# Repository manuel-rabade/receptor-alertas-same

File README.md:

# Receptor alertas SAME

Este deposito contiene el diseño de hardware y código fuente de mi trabajo de tesis, titulado [Sistema embebido para recibir alertas de riesgo codificadas con el protocolo SAME](http://www.ptolomeo.unam.mx:8080/xmlui/handle/RepoFi/18971), el cual realice para obtener el título de Ingeniero en Computación en la Facultad de Ingeniería de la Universidad Nacional Autónoma de México.

Como resultado de mi proyecto de titulación, se desarrolló un sistema embebido capaz de recibir alertas de riesgo transmitidas mediante el protocolo SAME y difundirlas a través de medios visuales, auditivos o electrónicos. Además, se documentan las bases técnicas para el desarrollo de productos o servicios que amplíen el aprovechamiento y la cobertura de los sistemas de alerta de riesgos.

## Organización

- [hardware](hardware): Diagrama esquemático, diseño de la placa electrónica y lista de componentes electrónicos del receptor.
- [software](software): Implementación del software del receptor. Código fuente de las pruebas unitarias y de integración.
- [logger](logger): Scripts y configuración para recolectar registros de operación.
- [prototipo](prototipo): Diagrama esquemático y software del prototipo del receptor.

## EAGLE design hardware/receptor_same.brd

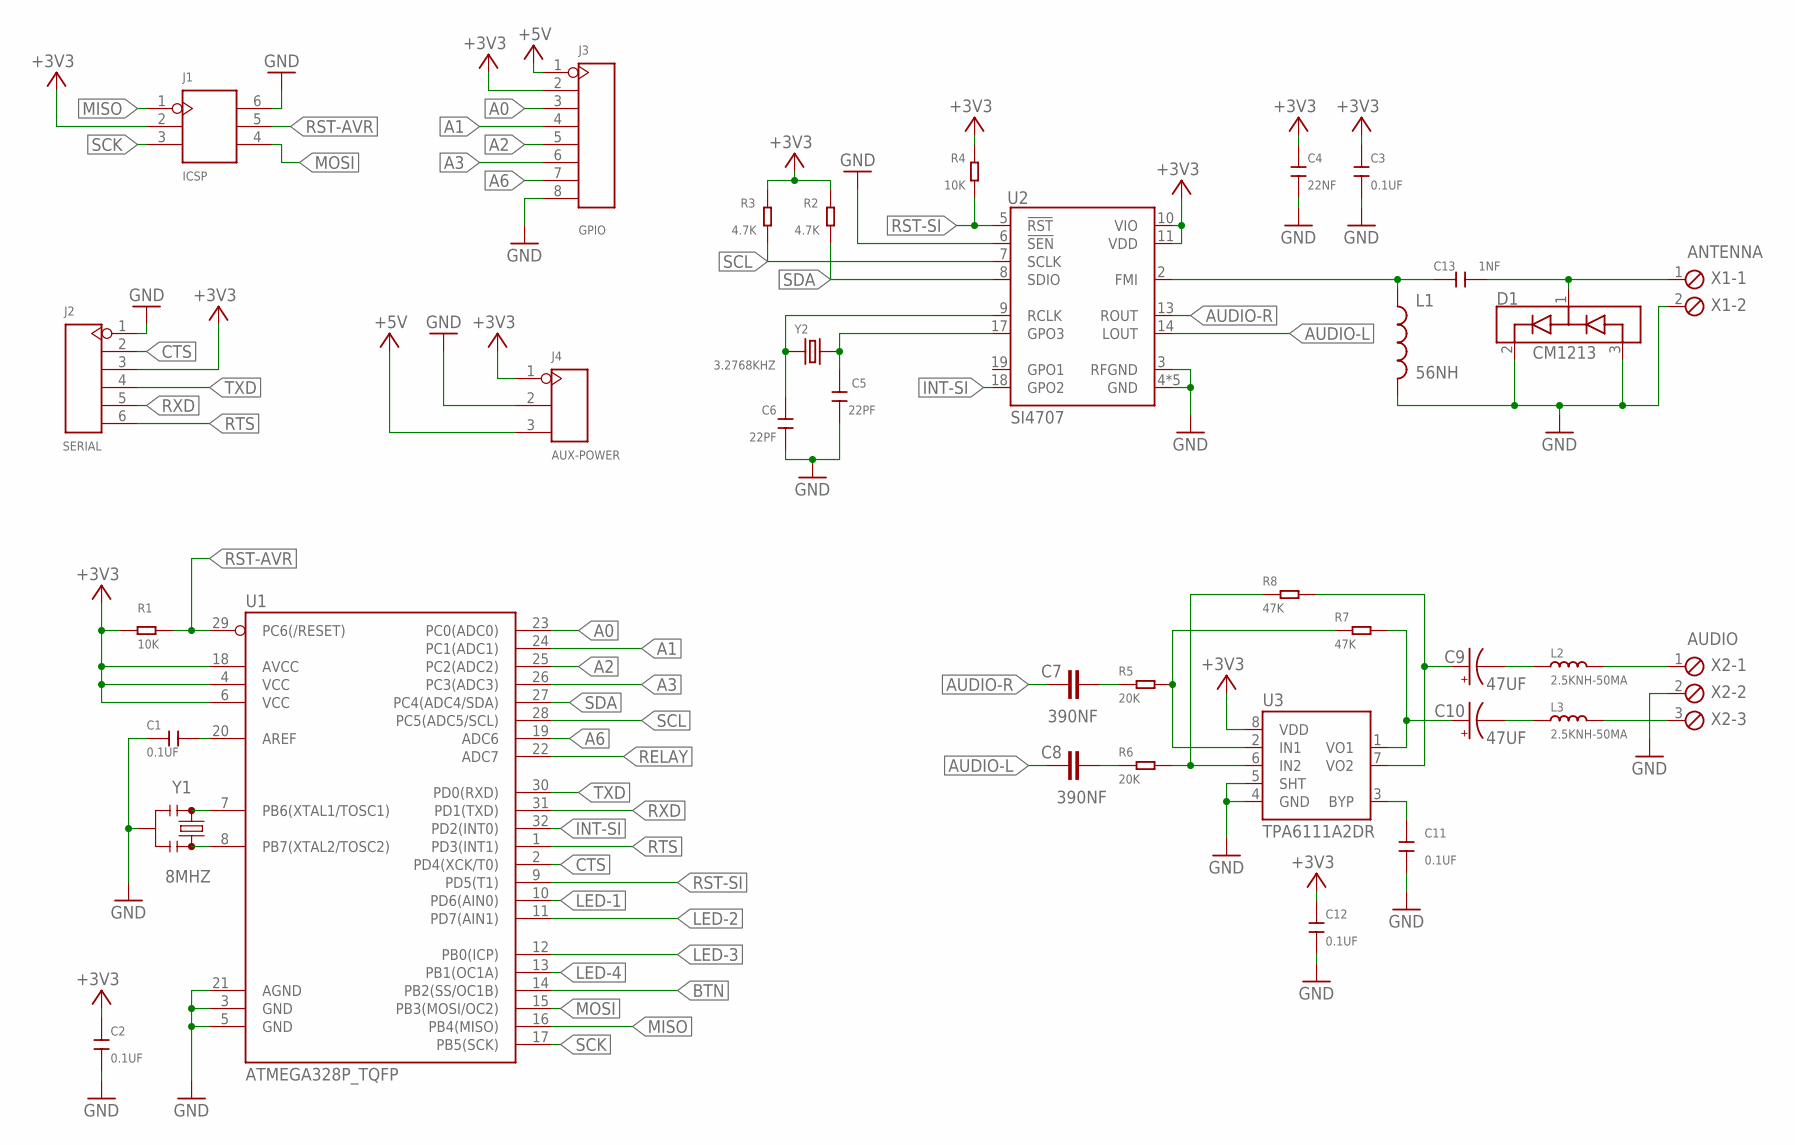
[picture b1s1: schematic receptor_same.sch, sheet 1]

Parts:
C1, C2, C3, C11, C12: 0.1UF; C0603
C4: 22NF; C0603
C5, C6: 22PF; C0603
C7, C8: 390NF; 0603; MPN CC0603KRX7R6BB394
C9, C10: 47UF; EIA3528; MPN TAJB476K010RNJ
C13: 1NF; C0603
D1: CM1213; SPARKFUN-DISCRETESEMI_SOT23-3; MPN CM1213A-01SO
J1: ICSP; H2X3-2.54
J2: SERIAL; H6-2.54
J3: GPIO; H8-2.54
J4: AUX-POWER; H3-2.54; MPN P125-1103A1BS116A1
L1: 56NH; SPARKFUN-PASSIVES_0603; MPN SDCL1608C56NJTDF
L2, L3: 2.5KNH-50MA; L0402; MPN BLM18BD252SN1D
R1, R4: 10K; R0603
R2, R3: 4.7K; R0603
R5, R6: 20K; R0603
R7, R8: 47K; R0603
U1: ATMEGA328P_TQFP; TQFP32-08; MPN ATMEGA328P-AU
U2: SI4707; SPARKFUN-RF_SI470X; MPN SI4707-B20-GM
U3: TPA6111A2DR; SO08; MPN TPA6111A2DR
X1: ANTENNA; 2POL254; MPN 1725656
X2: AUDIO; 3POL254; MPN 1725669
Y1: 8MHZ; RESONATOR-SMD-3.2X1.3; MPN CSTCE8M00G55-R0
Y2: 3.2768KHZ; X2-SMD-L2.0X1.2X0.55MM

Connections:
+3V3: C2.1, C3.1, C4.1, C12.1, J1.2, J2.3, J3.2, J4.1, R1.2, R2.1, R3.1, R4.1, U1.4 (VCC), U1.6 (VCC), U1.18 (AVCC), U2.10 (VIO), U2.11 (VDD), U3.8 (VDD); also elsewhere on the board
+5V: J3.1, J4.3; also elsewhere on the board
A0: J3.3, U1.23 (PC0(ADC0))
A1: J3.4, U1.24 (PC1(ADC1))
A2: J3.5, U1.25 (PC2(ADC2))
A3: J3.6, U1.26 (PC3(ADC3))
A6: J3.7, U1.19 (ADC6)
AUDIO-L: C8.1, U2.14 (LOUT)
AUDIO-R: C7.1, U2.13 (ROUT)
BTN: U1.14 (PB2(SS/OC1B)); also elsewhere on the board
CTS: J2.2, U1.2 (PD4(XCK/T0))
GND: C1.1, C2.2, C3.2, C4.2, C5.1, C6.1, C11.2, C12.2, D1.2 (VP), D1.3 (VN), J1.6, J2.1, J3.8, J4.2, L1.2, U1.3 (GND), U1.5 (GND), U1.21 (AGND), U2.3 (RFGND), U2.4 (GND), U2.6 (!SEN), U2.12 (GND), U2.15 (GND), U2.16 (GND), U2.21 (GND), U3.4 (GND), U3.5 (SHT), X1.2, X2.2, Y1.2; also elsewhere on the board
INT-SI: U1.32 (PD2(INT0)), U2.18 (GPO2)
L: L2.2, X2.1
LED-1: U1.10 (PD6(AIN0)); also elsewhere on the board
LED-2: U1.11 (PD7(AIN1)); also elsewhere on the board
LED-3: U1.12 (PB0(ICP)); also elsewhere on the board
LED-4: U1.13 (PB1(OC1A)); also elsewhere on the board
MISO: J1.1, U1.16 (PB4(MISO))
MOSI: J1.4, U1.15 (PB3(MOSI/OC2))
unnamed: U1.7 (PB6(XTAL1/TOSC1)), Y1.1
unnamed: U1.8 (PB7(XTAL2/TOSC2)), Y1.3
unnamed: C1.2, U1.20 (AREF)
unnamed: C5.2, U2.17 (GPO3), Y2.2
unnamed: C6.2, U2.9 (RCLK), Y2.1
unnamed: C13.1, L1.1, U2.2 (FMI)
unnamed: C7.2, R5.1
unnamed: C8.2, R6.1
unnamed: C11.1, U3.3 (BYP)
unnamed: R5.2, R7.1, U3.2 (IN1)
unnamed: C10.A (+), R7.2, U3.1 (VO1)
unnamed: R6.2, R8.1, U3.6 (IN2)
unnamed: C9.A (+), R8.2, U3.7 (VO2)
unnamed: C9.C (-), L2.1
unnamed: C10.C (-), L3.1
unnamed: C13.2, D1.1 (CH1), X1.1
R: L3.2, X2.3
RELAY: U1.22 (ADC7); also elsewhere on the board
RST-AVR: J1.5, R1.1, U1.29 (PC6(/RESET))
RST-SI: R4.2, U1.9 (PD5(T1)), U2.5 (!RST)
RTS: J2.6, U1.1 (PD3(INT1))
RXD: J2.5, U1.31 (PD1(TXD))
SCK: J1.3, U1.17 (PB5(SCK))
SCL: R3.2, U1.28 (PC5(ADC5/SCL)), U2.7 (SCLK)
SDA: R2.2, U1.27 (PC4(ADC4/SDA)), U2.8 (SDIO)
TXD: J2.4, U1.30 (PD0(RXD))

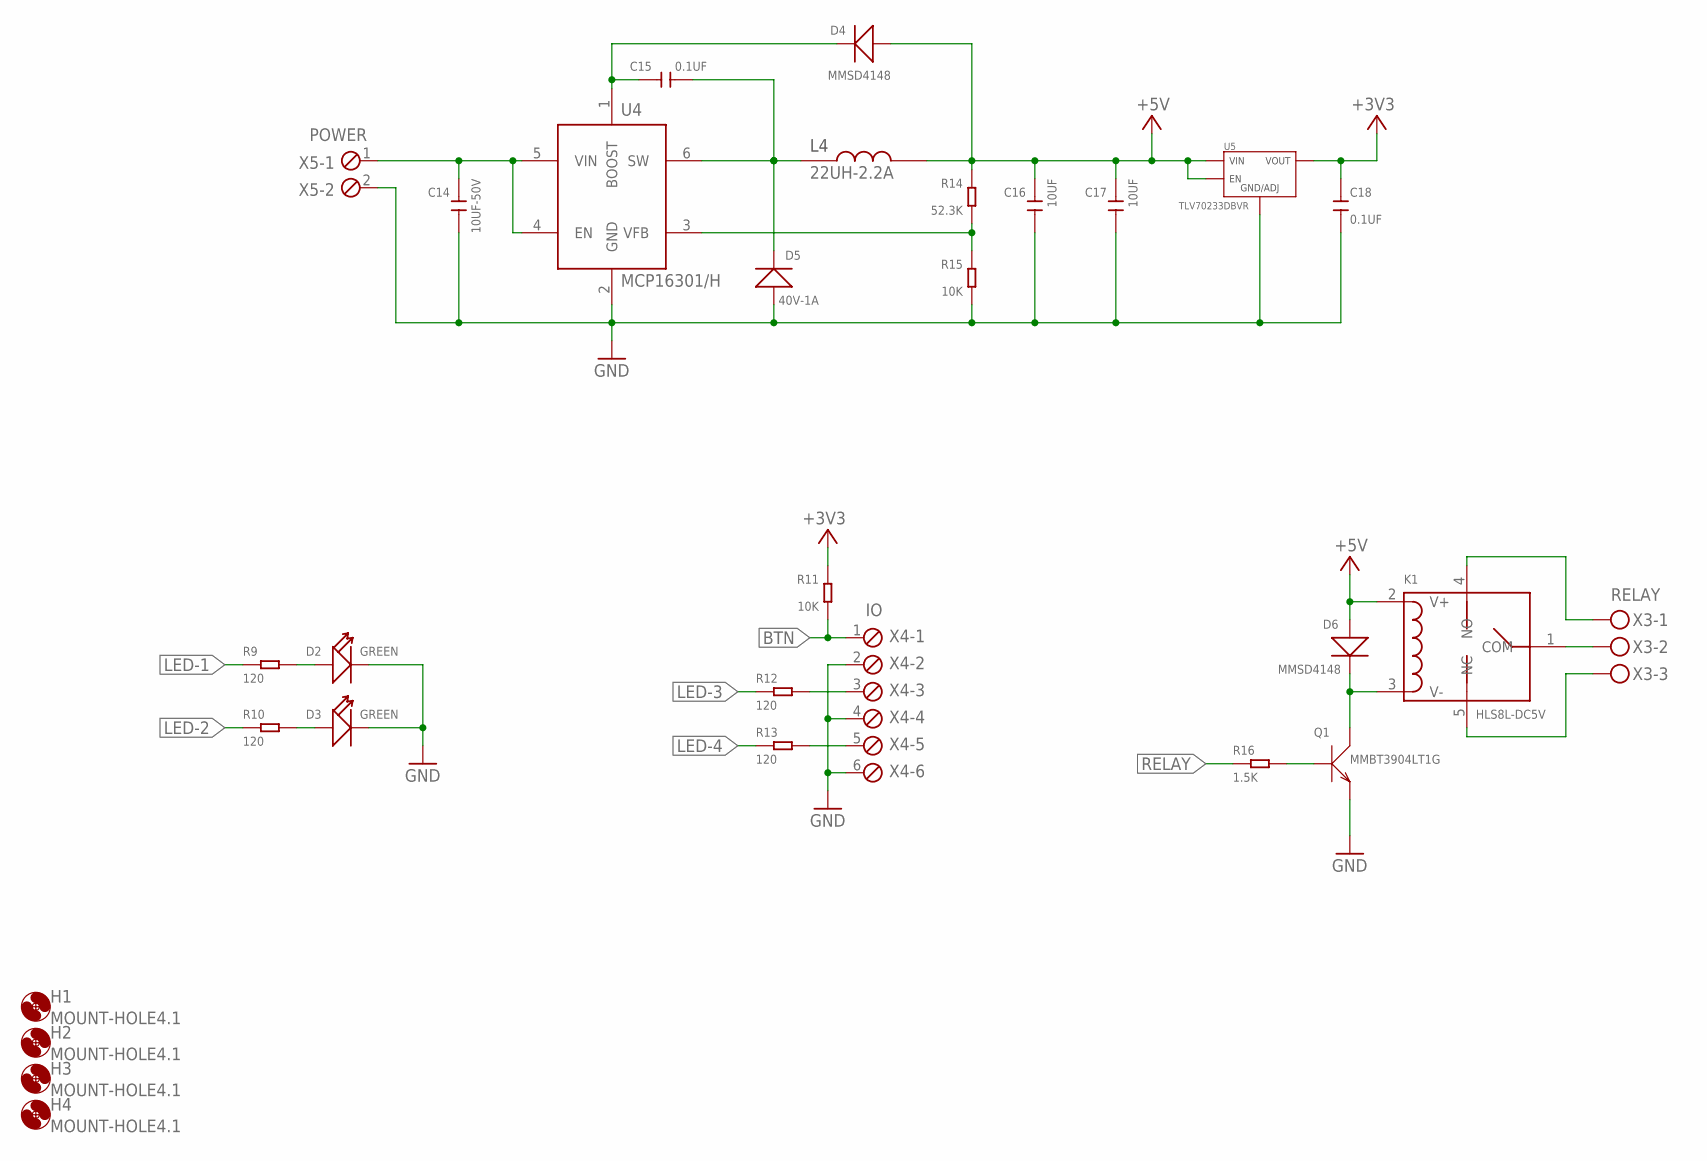
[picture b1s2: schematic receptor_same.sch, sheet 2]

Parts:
C14: 10UF-50V; C1206; MPN CL31A106KBHNNNE
C15, C18: 0.1UF; C0603
C16, C17: 10UF; C0603
D2, D3: GREEN; LED-0805
D4, D6: MMSD4148; SOD-123
D5: 40V-1A; DO-214AC
H1, H2, H3, H4: MOUNT-HOLE4.1; 4,1
K1: HLS8L-DC5V; REY5-19.0X15.0X15.0MM; MPN HLS8L-DC5V-S-C
L4: 22UH-2.2A; L2826; MPN SHC0603-220M
Q1: MMBT3904LT1G; SOT-23
R9, R10, R12, R13: 120; R0805; MPN RC0805JR-07120RL
R11, R15: 10K; R0603
R14: 52.3K; R0603; MPN WR06X5232FTL
R16: 1.5K; R0603
U4: MCP16301/H; SOT23-6; MPN MCP16301T-I/CHY
U5: TLV70233DBVR; SOT-23-5; MPN TLV70233DBVR
X3: RELAY; MKDSN1,5/3-5,08; MPN 1715734
X4: IO; 6POL254; MPN 1725698
X5: POWER; 2POL254; MPN 1725656

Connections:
+3V3: C18.1, R11.1, U5.P$5 (VOUT); also elsewhere on the board
+5V: C16.2, C17.2, D4.+, D6.+, K1.2 (V+), L4.P$2, R14.2, U5.P$1 (VIN), U5.P$3 (EN); also elsewhere on the board
BTN: R11.2, X4.1; also elsewhere on the board
GND: C14.1, C16.1, C17.1, C18.2, D2.-, D3.-, D5.1 (+), Q1.2 (E), R15.2, U4.2 (GND), U5.P$2 (GND/ADJ), X4.2, X4.4, X4.6, X5.2; also elsewhere on the board
LED-1: R9.1; also elsewhere on the board
LED-2: R10.1; also elsewhere on the board
LED-3: R12.1; also elsewhere on the board
LED-4: R13.1; also elsewhere on the board
unnamed: R12.2, X4.3
unnamed: D3.+, R10.2
unnamed: D2.+, R9.2
unnamed: R13.2, X4.5
unnamed: C15.2, D4.-, U4.1 (BOOST)
unnamed: K1.1 (COM), X3.2
unnamed: R14.1, R15.1, U4.3 (VFB)
unnamed: K1.4 (NO), X3.1
unnamed: K1.5 (NC), X3.3
unnamed: D6.-, K1.3 (V-), Q1.3 (C)
unnamed: Q1.1 (B), R16.2
RELAY: R16.1; also elsewhere on the board
SW: C15.1, D5.2 (-), L4.P$1, U4.6 (SW)
VIN: C14.2, U4.4 (EN), U4.5 (VIN), X5.1

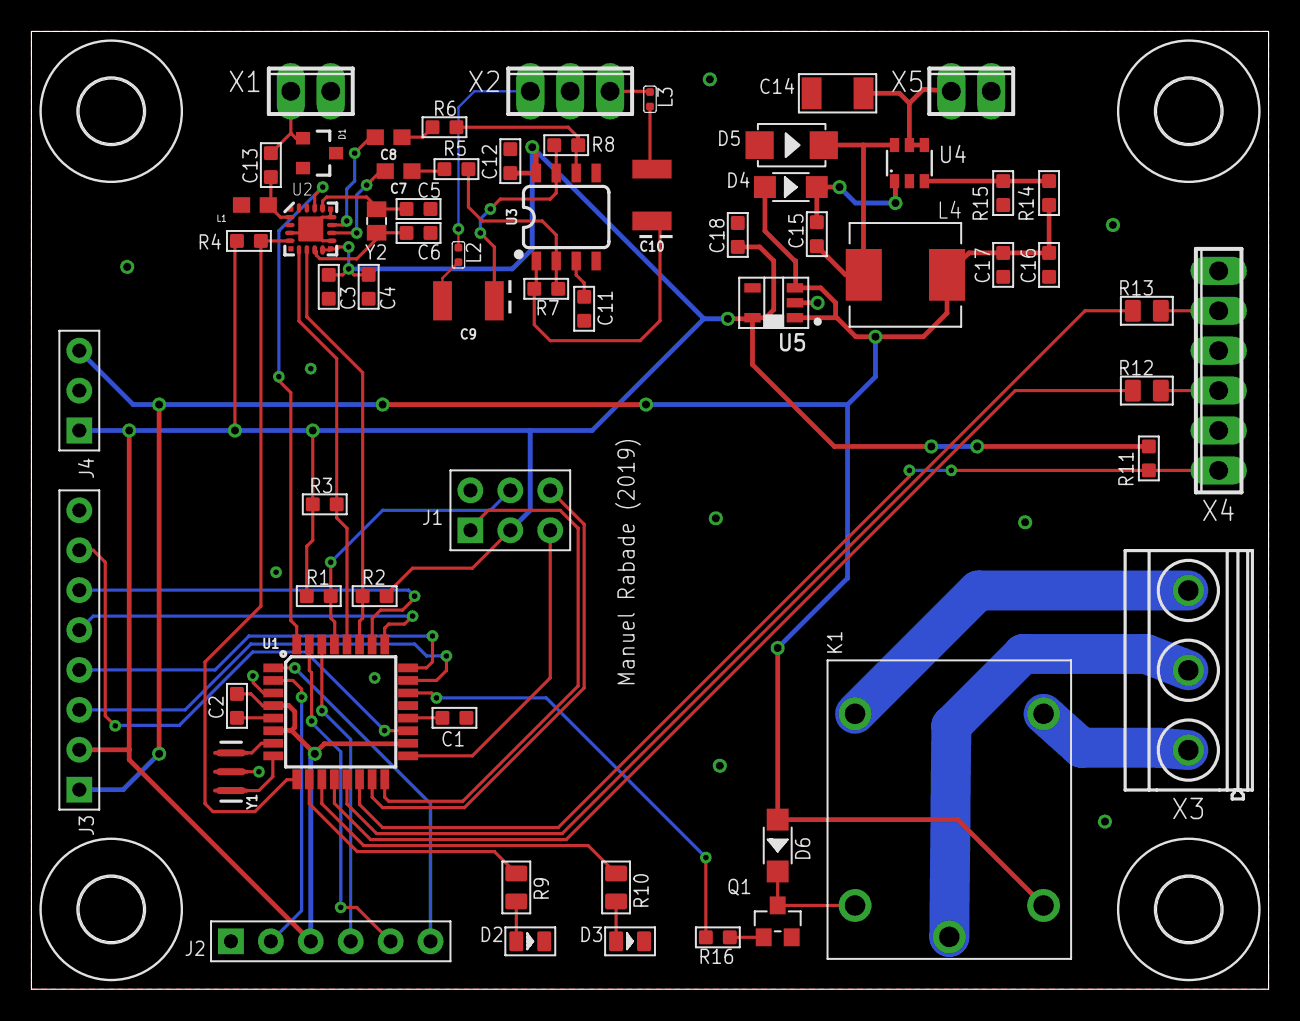
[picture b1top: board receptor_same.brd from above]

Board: 2 copper layers, 78.7 x 61.0 mm, 66 parts (0 on the bottom side), 59 nets.

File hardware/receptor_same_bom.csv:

"Qty";"Value";"Device";"Package";"Parts";"Description";"HOUSEPART";"MF";"MPN";"OC_FARNELL";"OC_NEWARK";"POPULATE";"PROD_ID";"SPICEPREFIX";"URL";"VALUE";
"7";"0.1UF";"CERAMIC-100NF-50V-10%-X7R(0603)";"C0603";"C1, C2, C3, C11, C12, C15, C18";"302010138";"";"";"CC0603KRX7R9BB104";"";"";"";"";"";"";"100nf";
"1";"1.5K";"SMD-RES-1.5K-5%-1/10W(0603)";"R0603";"R16";"301010114";"";"";"RC0603JR-071K5L";"";"";"";"";"";"";"1.5K 1/10W";
"4";"10K";"SMD-RES-10K-5%-1/10W(0603)";"R0603";"R1, R4, R11, R15";"301010293";"";"";"RC0603JR-0710KL";"";"";"";"";"";"";"10K 1/10W";
"2";"10UF";"CERAMIC-10UF-6.3V-20%-X5R(0603)";"C0603";"C16, C17";"302010286";"";"";"CC0603MRX5R5BB106";"";"";"";"";"";"";"10UF 6.3V";
"1";"10UF-50V";"CERAMIC-10UF-25V-10%-X5R(1206)";"C1206";"C14";"302010181";"";"";"CL31A106KBHNNNE";"";"";"";"";"";"";"10uf";
"4";"120";"SMD-RES-120R-5%-1/8W(0805)";"R0805";"R9, R10, R12, R13";"301012183";"";"";"RC0805JR-07120RL";"";"";"";"";"";"";"1K";
"1";"1NF";"CERAMIC-1NF-50V-5%-C0G(0603)";"C0603";"C13";"302010341";"";"";"GRM1885C1H102JA01D";"";"";"";"";"";"";"1nf";
"2";"2.5KNH-50MA";"SMD-INDUCTOR-4.7NH-0.3NH-300MA(0402)";"L0402";"L2, L3";"303010037";"";"";"BLM18BD252SN1D";"";"";"";"";"L";"";"4.7NH-300MA";
"2";"20K";"SMD-RES-20K-1%-1/10W(0603)";"R0603";"R5, R6";"301011971";"";"";"RC0603FR-0720KL";"";"";"";"";"R";"";"20K";
"1";"22NF";"CERAMIC-22NF-50V-10%-X7R(0603)";"C0603";"C4";"302010095";"";"";"CC0603KRX7R9BB223";"";"";"";"";"";"";"22nf";
"2";"22PF";"CERAMIC-22PF-50V-5%-NPO(0603)";"C0603";"C5, C6";"302010143";"";"";"CC0603JRNPO9BN220";"";"";"";"";"C";"";"22pf";
"1";"22UH-2.2A";"303010525_22UH_7.1X6.6MM";"L2826";"L4";"SHC0603-220M, SMD Inductor 22uH-20%-0.139R-2.2A;2P-L7.1*W6.6*H3.0mm, SKU: 303010525";"";"";"SHC0603-220M ";"";"";"";"";"";"";"";
"1";"3.2768KHZ";"SMD-CRYSTAL-32.768KHZ-12.5PF-20PPM-90K(2P-L2.0X1.2MM)";"X2-SMD-L2.0X1.2X0.55MM";"Y2";"306010020";"";"";"FC-12M";"";"";"";"";"B";"";"3.2768KHZ";
"2";"390NF";"390NF-0603-10V-10%";"0603";"C7, C8";"0.39uF/390nF ceramic capacitors";"";"";"CC0603KRX7R6BB394";"";"";"";"CAP-10986";"C";"";"390nF";
"2";"4.7K";"SMD-RES-4.7K-5%-1/10W(0603)";"R0603";"R2, R3";"301010290";"";"";"RC0603JR-074K7L";"";"";"";"";"";"";"4.7K";
"1";"40V-1A";"SMD-DIODE-SCHOTTKY-40V-1A(DO-214AC)";"DO-214AC";"D5";"304020027";"";"";"1N5819";"";"";"";"";"";"";"40V-1A";
"2";"47K";"SMD-RES-47K-5%-1/10W(0603)";"R0603";"R7, R8";"301010084";"";"";"RC0603JR-0747KL";"";"";"";"";"R";"";"47K";
"2";"47UF";"47UF-POLAR-EIA3528-10V-10%";"EIA3528";"C9, C10";"47µF polarized capacitors";"";"";"TAJB476K010RNJ";"";"";"";"CAP-08310";"C";"";"47uF";
"1";"52.3K";"SMD-RES-51K-5%-1/10W(0603)";"R0603";"R14";"301012135";"";"";"WR06X5232FTL";"";"";"";"";"";"";"51K";
"1";"56NH";"SPARKFUN-PASSIVES_INDUCTOR0603";"SPARKFUN-PASSIVES_0603";"L1";"Inductors";"";"";"SDCL1608C56NJTDF";"";"";"";"";"";"";"";
"1";"8MHZ";"RESONATOR-8MHZSMD_3.2X1.3";"RESONATOR-SMD-3.2X1.3";"Y1";"8MHz Resonator";"";"";"CSTCE8M00G55-R0";"";"";"";"XTAL-08895";"";"";"8MHz";
"1";"ANTENNA";"MPT2";"2POL254";"X1";"PHOENIX CONNECTOR";"";"";"1725656";"unknown";"unknown";"";"";"";"";"";
"1";"ATMEGA328P_TQFP";"ATMEGA328P_TQFP";"TQFP32-08";"U1";"Popular 328P in QFP";"";"";"ATMEGA328P-AU";"";"";"";"IC-09069";"";"";"ATMEGA328P_TQFP";
"1";"AUDIO";"MPT3";"3POL254";"X2";"PHOENIX CONNECTOR";"";"";"1725669";"unknown";"unknown";"";"";"X";"";"";
"1";"AUX-POWER";"DIP-BLACK-MALE-HEADER-VERT(3P-2.54)";"H3-2.54";"J4";"320020079";"";"";"P125-1103A1BS116A1";"";"";"";"";"";"";"3p-2.54";
"1";"CM1213";"SPARKFUN-DISCRETESEMI_CM1213";"SPARKFUN-DISCRETESEMI_SOT23-3";"D1";"";"";"";"CM1213A-01SO";"";"";"";"";"";"https://www.digikey.com.mx/product-detail/en/on-semiconducto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";"";
"1";"GPIO";"DIP-BLACK-MALE-HEADER-VERT(8P-2.54)";"H8-2.54";"J3";"320020080";"";"";"P125-1108A1BS116A1";"";"";"";"";"";"";"8p-2.54";
"2";"GREEN";"SMD-LED-CLEAR-GREEN(0805)";"LED-0805";"D2, D3";"304090057";"";"";"17-215SYGC/S530-E2/TR8";"";"";"";"";"";"";"GREEN-0805";
"1";"HLS8L-DC5V";"RELAY-HLS8L-DC5V-S-CHLS8L-DC5V-S-C";"REY5-19.0X15.0X15.0MM";"K1";"315030000";"";"";"HLS8L-DC5V-S-C";"";"";"";"";"";"";"";
"1";"ICSP";"DIP-BLACK-MALE-HEADER(2X3P-2.54）-2.54";"H2X3-2.54";"J1";"320020077";"";"";"P125-12A1BS116A1";"";"";"";"";"";"";"2x3p-2.54";
"1";"IO";"MPT6";"6POL254";"X4";"PHOENIX CONNECTOR";"";"";"1725698";"unknown";"unknown";"";"";"";"";"";
"1";"MCP16301/H";"MCP16301/H";"SOT23-6";"U4";"High-Voltage Input Integrated Switch Step-Down Regulator";"";"";"MCP16301T-I/CHY";"";"";"";"";"";"";"";
"1";"MMBT3904LT1G";"SMD-TRANSISTORS-NPN-40V-200MA-MMBT3904LT1G(SOT-23)";"SOT-23";"Q1";"305010013";"";"";"MMBT3904LT1G";"";"";"";"";"";"";"MMBT3904LT1G";
"2";"MMSD4148";"SMD-DIODE-100V-200MA(SOD-123)";"SOD-123";"D4, D6";"304010007";"";"";"MMSD4148";"";"";"";"";"";"";"MMSD4148-sod123";
"4";"MOUNT-HOLE4.1";"MOUNT-HOLE4.1";"4,1";"H1, H2, H3, H4";"MOUNTING HOLE with drill center marker";"";"";"";"";"";"";"";"";"";"";
"1";"POWER";"MPT2";"2POL254";"X5";"PHOENIX CONNECTOR";"";"";"1725656";"unknown";"unknown";"";"";"";"";"";
"1";"RELAY";"MKDSN1,5/3-5,08";"MKDSN1,5/3-5,08";"X3";"MKDSN 1,5/ 3-5,08 Printklemme";"";"";"1715734";"";"";"";"";"";"";"";
"1";"SERIAL";"DIP-BLACK-MALE-HEADER(6P-2.54)";"H6-2.54";"J2";"320020078";"";"";"P125-1106A1BS116A1";"";"";"";"";"X";"";"6p-2.54";
"1";"SI4707";"SPARKFUN-RF_SI4707";"SPARKFUN-RF_SI470X";"U2";"Silicon Labs Si4707 Weather Band and SAME Data Receiver";"";"";"SI4707-B20-GM";"";"";"";"";"X";"https://www.digikey.com/product-detail/en/silicon-labs/SI470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";"";
"1";"TLV70233DBVR";"TLV70233PDBVR";"SOT-23-5";"U5";"Manufacturer Part #: TLV702";"YES";"";"TLV70233DBVR";"";"";"1";"";"";"";"MF-REG-SOT235-3.3V-300mA";
"1";"TPA6111A2DR";"TPA6111SMD-T";"SO08";"U3";"TPA6111A2";"";"";"TPA6111A2DR";"";"";"";"IC-10149";"X";"https://www.digikey.com/product-detail/en/texas-instruments/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";"TPA6111A2DR";

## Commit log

2019-05-06 mcu y xtal en sch
2019-05-09 avances mcu
2019-05-09 icsp
2019-05-09 separamos icsp
2019-05-10 ignoramos backups
2019-05-10 biblioteca si4707 de sparkfun
2019-05-10 avances si4707 y conctor puerto serial
2019-05-11 borramos biblioteca si4707 y agregamos la del breakout de sparkfun completo
2019-05-12 terminamos si4707, tda611, io, gpio y leds
2019-05-14 bibliotecas de partes
2019-05-14 fuente de poder
2019-05-14 120 para resistencias de leds (12.5 mA)
2019-05-14 bibliotecas de eagle en hardware
2019-05-14 segunda hoja: relay y aux power
2019-05-14 fix mpn conector 3 pines
2019-05-15 ajustes bom y posicion en hoja
2019-05-15 ajustamos values a mayusculas
2019-05-15 ajutes values caps
2019-05-16 puntos de montaje en esquematico y pasa el erc
2019-05-16 arrancamos el ruteo!
2019-05-16 avances si4707 y audio
2019-05-16 avances ruteo si + amp
2019-05-16 avances pcba
2019-05-26 pcb terminado
2019-05-27 ultimos ajustes pcb
2019-05-27 archivos de fabricacion
2019-06-24 misc esquematico
2020-04-13 software tests
2020-05-01 receptor same
2020-05-05 recepcion de mensajes same
2020-06-06 clase IO
2020-06-06 pruebas clase IO
2020-06-06 integracion clase IO
2020-06-09 clase command
2020-06-15 ordenamos definiciones
2020-06-15 modo c++
2020-06-15 incio integración Command
2020-06-15 inicio clase Config
2020-06-21 clase config hasta codigos de evento y area, pendiente save y reload con pruebas
2020-06-21 set defaults y fixes para busqueda en listas vacias
2020-06-21 misc y doc
2020-06-23 ajuste debug volume
2020-06-23 misc
2020-06-23 integracion Config en setup y limpieza
2020-06-27 tabla de comandos y getCmd
2020-06-27 fix comparacion getCmd
2020-06-28 avances comandos
2020-06-28 mejoramos tabla comandos + dump
2020-06-28 simplificamos comandos
2020-06-28 volumen de 0 a 10, fix setAudio y setRelay, clarificar periodo rmt y rwt
2020-06-28 avances y optimizacion memoria
2020-07-04 pruebas codigo de area con comodin
2020-07-04 buscar codigo de area con comodin y periodos rwt y rmt en millis
2020-07-04 filtros de area y evento por mensaje, timer same, rwt y rmt
2020-07-05 leds begin, error, wait, wait rt y alert
2020-07-05 ledRefresh -> ledsRefresh
2020-07-05 audio conf 0 y 1
2020-07-06 mock radio
2020-08-28 guardamos periodos de tiempos en millis, audio 2
2020-08-30 eliminamos configuracion audio
2020-09-07 MockRadio!
2020-09-07 muchas mejoras!
2020-09-07 typo
2020-09-07 simplificamos fsm mockradio
2020-09-07 desactivamos mockradio
2021-04-17 raspberry pi logger
2022-07-24 fix comparacion bandera rwt dos veces en lugar de rmt
2022-07-26 fix mute
2023-01-16 pruebas de integracion para mejoras
2023-01-16 procesamos dos cabeceras si recibimos un fin de mensaje
2023-01-16 nueva configuracion sasmex
2023-01-16 test configuracion sasmex
2023-01-17 configuracion same para defaults
2023-01-18 soporte para reproductor de audio externo
2023-01-29 modo sasmex -> cdmx
2023-01-29 comando cdmx
2023-01-29 avanzamos version de configuracion
2023-01-29 eliminamos configuracion de IO
2023-01-29 sync con io y config
2023-01-29 configuracion cdmx
2023-01-29 alerta cdmx
2023-01-29 fix mock
2023-04-18 misc MockRadio
2023-04-18 ajustamos AUDIO_PLAY_TIME a 10 ms
2023-04-19 elimnamos comando audio
2023-04-19 ajustes finales
2023-04-19 fix configurar cdmx
2023-10-05 esquematico y software del prototipo del receptor de alertas
2023-10-23 borarmos prueba del prototipo repetida
2023-10-23 ignoramos carpeta vscode
2024-03-23 pulimos readme y agregamos liga a tesis

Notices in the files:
parts and their libraries:
SparkFun-Capacitors: Licensing: Creative Commons ShareAlike 4.0 International - https://creativecommons.org/licenses/by-sa/4.0
